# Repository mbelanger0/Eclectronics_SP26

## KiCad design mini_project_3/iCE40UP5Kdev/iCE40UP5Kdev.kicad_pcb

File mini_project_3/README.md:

# Mini Project 3 - iCE40UP5 Development Board

# Project Overview
The goal fo this project was to create a development board layout for the Lattice iCE40UP5 FPGA that is as close in size as possible to a Raspberry Pi Pico.

My implementation is located in the `iCE40UP5Kdev` directory.

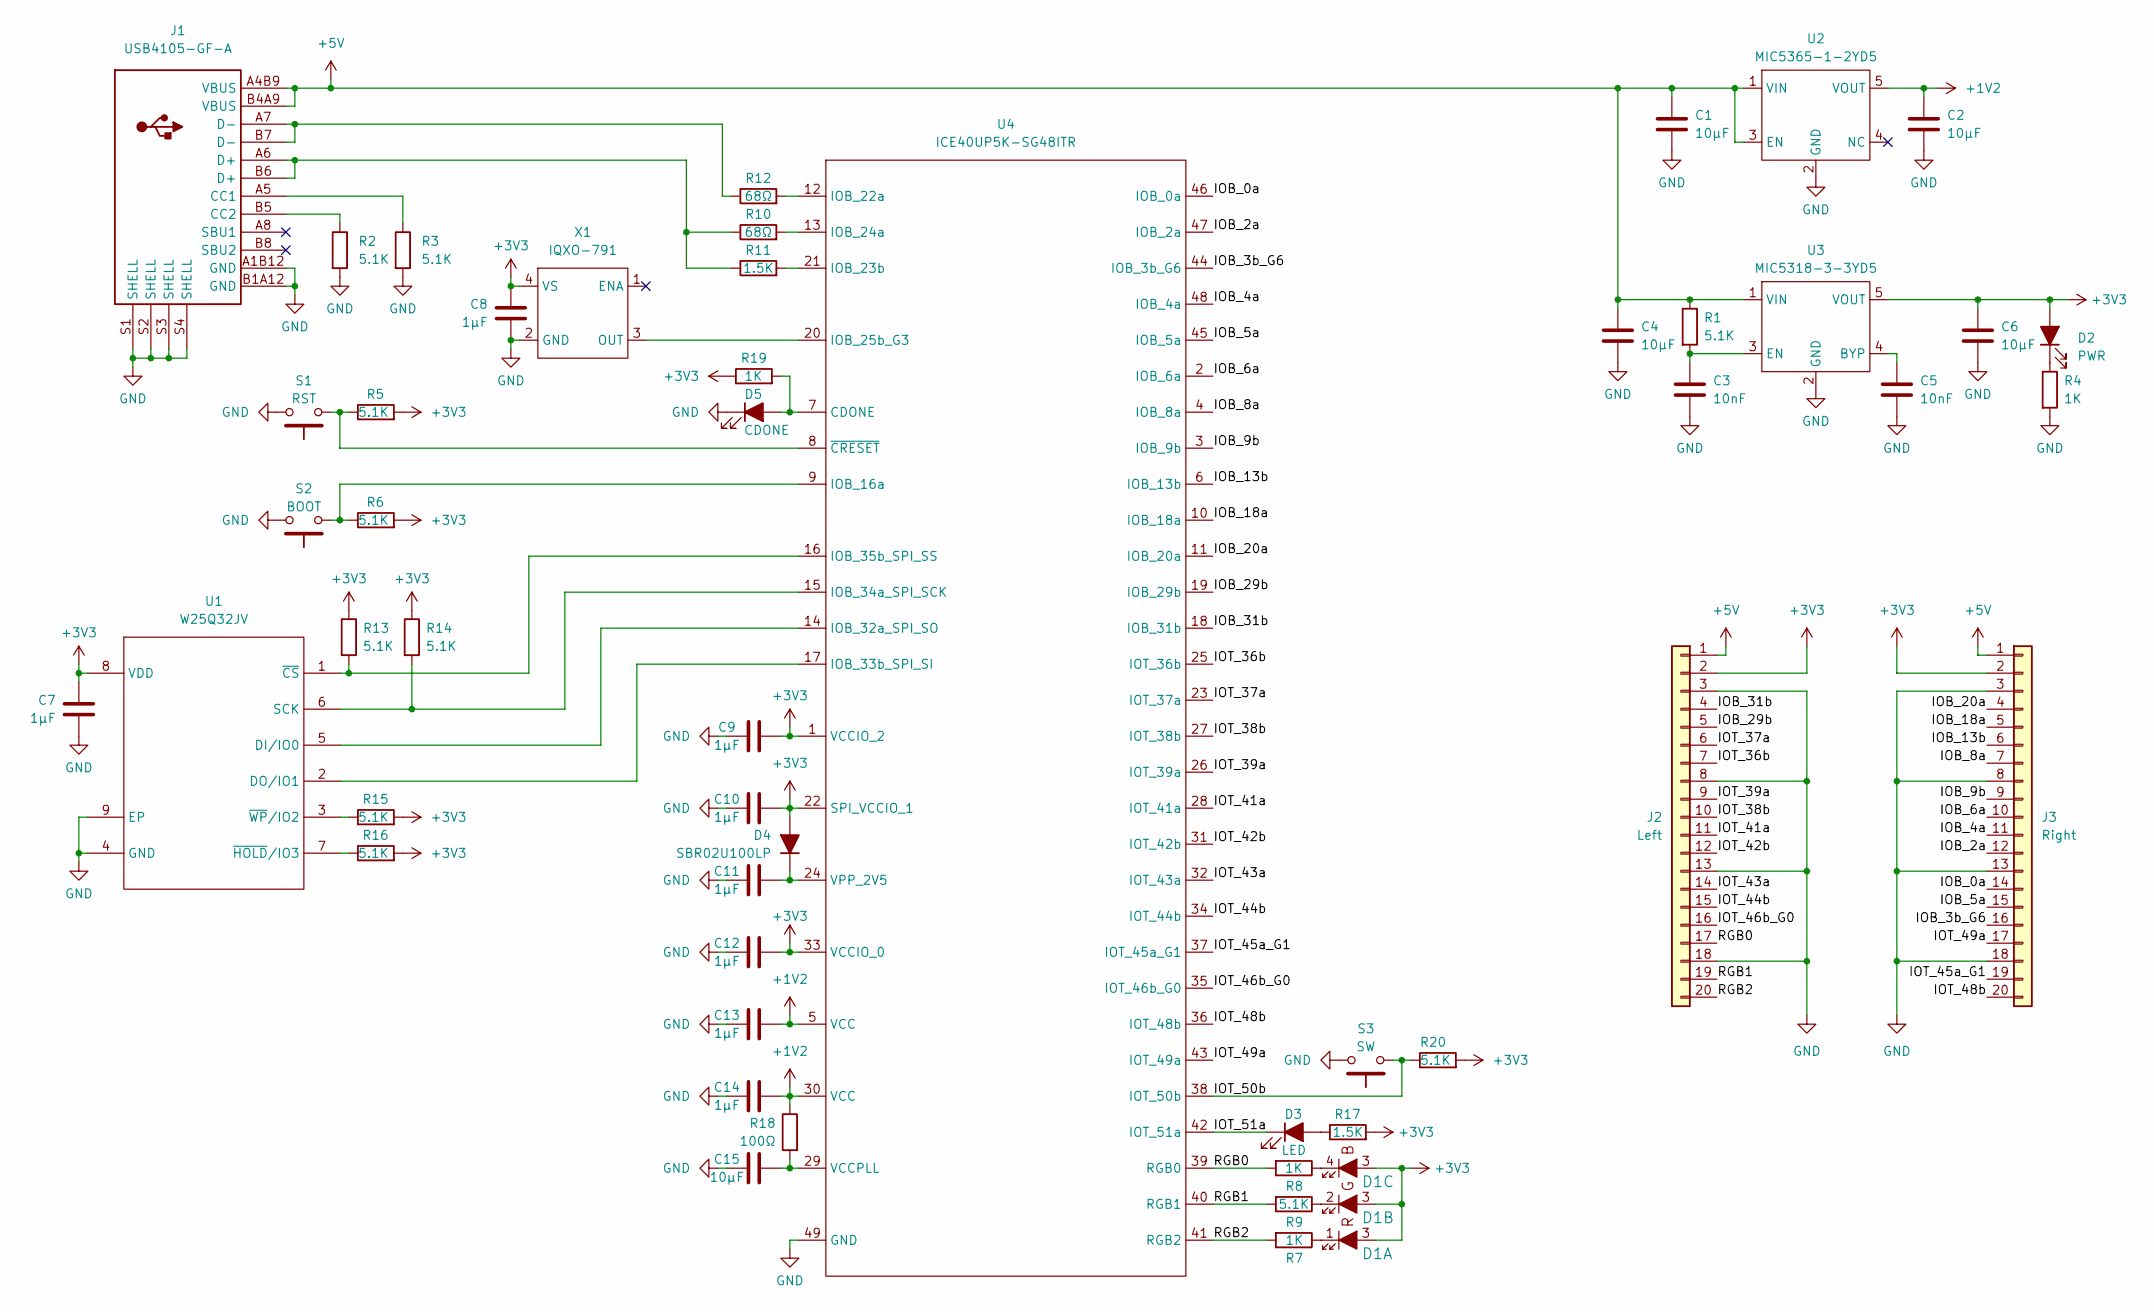
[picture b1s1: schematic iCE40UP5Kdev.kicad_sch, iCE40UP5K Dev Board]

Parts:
C1, C2, C4, C6, C15: 10µF; C_0603_1608Metric
C3, C5: 10nF; C_0603_1608Metric
C7, C8, C9, C10, C11, C12, C13, C14: 1µF; C_0402_1005Metric
D1: IN-S85TATRGB_ALT; IN-S85TATRGB
D2: PWR; LED_0805_2012Metric
D3: LED; LED_0805_2012Metric
D4: SBR02U100LP; D_0402_1005Metric
D5: CDONE; LED_0805_2012Metric
J1: USB4105-GF-A
J2: Left; PinHeader_1x20_P2.54mm_Vertical
J3: Right; PinHeader_1x20_P2.54mm_Vertical
R1, R2, R3, R5, R6, R9, R20: 5.1K; R_0603_1608Metric
R4, R7, R8, R19: 1K; R_0603_1608Metric
R10, R12: 68Ω; R_0402_1005Metric
R11: 1.5K; R_0402_1005Metric
R13, R14, R15, R16: 5.1K; R_0402_1005Metric
R17: 1.5K; R_0603_1608Metric
R18: 100Ω; R_0402_1005Metric
S1: RST; SW_SPST_B3U-1000P
S2: BOOT; SW_SPST_B3U-1000P
S3: SW; SW_SPST_B3U-1000P
U1: W25Q32JV; WSON-8-1EP_6x5mm_P1.27mm_EP3.4x4.3mm
U2: MIC5365-1-2YD5; TSOT-23-5
U3: MIC5318-3-3YD5; TSOT-23-5
U4: ICE40UP5K-SG48ITR; QFN-48-1EP_7x7mm_P0.5mm_EP5.6x5.6mm
X1: IQXO-791

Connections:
+1V2: C2.1, C13.2, C14.2, R18.1, U2.5 (VOUT), U4.5 (VCC), U4.30 (VCC)
+3V3: C6.1, C7.1, C8.1, C9.2, C10.2, C12.2, D1.3, D2.2 (A), D4.2 (A), J2.2, J3.2, R5.2, R6.2, R13.1, R14.1, R15.2, R16.2, R17.2, R19.1, R20.2, U1.8 (VDD), U3.5 (VOUT), U4.1 (VCCIO_2), U4.22 (SPI_VCCIO_1), U4.33 (VCCIO_0), X1.4 (VS)
+5V: C1.1, C4.1, J1.A4B9 (VBUS), J1.B4A9 (VBUS), J2.1, J3.1, R1.1, U2.1 (VIN), U2.3 (EN), U3.1 (VIN)
/IOB_0a: J3.14, U4.46 (IOB_0a)
/IOB_2a: J3.12, U4.47 (IOB_2a)
/IOB_3b_G6: J3.16, U4.44 (IOB_3b_G6)
/IOB_4a: J3.11, U4.48 (IOB_4a)
/IOB_5a: J3.15, U4.45 (IOB_5a)
/IOB_6a: J3.10, U4.2 (IOB_6a)
/IOB_8a: J3.7, U4.4 (IOB_8a)
/IOB_9b: J3.9, U4.3 (IOB_9b)
/IOB_13b: J3.6, U4.6 (IOB_13b)
/IOB_18a: J3.5, U4.10 (IOB_18a)
/IOB_20a: J3.4, U4.11 (IOB_20a)
/IOB_29b: J2.5, U4.19 (IOB_29b)
/IOB_31b: J2.4, U4.18 (IOB_31b)
/IOT_36b: J2.7, U4.25 (IOT_36b)
/IOT_37a: J2.6, U4.23 (IOT_37a)
/IOT_38b: J2.10, U4.27 (IOT_38b)
/IOT_39a: J2.9, U4.26 (IOT_39a)
/IOT_41a: J2.11, U4.28 (IOT_41a)
/IOT_42b: J2.12, U4.31 (IOT_42b)
/IOT_43a: J2.14, U4.32 (IOT_43a)
/IOT_44b: J2.15, U4.34 (IOT_44b)
/IOT_45a_G1: J3.19, U4.37 (IOT_45a_G1)
/IOT_46b_G0: J2.16, U4.35 (IOT_46b_G0)
/IOT_48b: J3.20, U4.36 (IOT_48b)
/IOT_49a: J3.17, U4.43 (IOT_49a)
/IOT_50b: R20.1, S3.1, U4.38 (IOT_50b)
/IOT_51a: D3.1 (K), U4.42 (IOT_51a)
/RGB0: J2.17, R8.2, U4.39 (RGB0)
/RGB1: J2.19, R9.2, U4.40 (RGB1)
/RGB2: J2.20, R7.2, U4.41 (RGB2)
GND: C1.2, C2.2, C3.2, C4.2, C5.2, C6.2, C7.2, C8.2, C9.1, C10.1, C11.1, C12.1, C13.1, C14.1, C15.1, D5.1 (K), J1.A1B12 (GND), J1.B1A12 (GND), J1.S1 (SHELL), J1.S2 (SHELL), J1.S3 (SHELL), J1.S4 (SHELL), J2.3, J2.8, J2.13, J2.18, J3.3, J3.8, J3.13, J3.18, R2.2, R3.2, R4.2, S1.2, S2.2, S3.2, U1.4 (GND), U1.9 (EP), U2.2 (GND), U3.2 (GND), U4.49 (GND), X1.2 (GND)
unnamed: D1.1, R7.1
unnamed: D1.2, R9.1
unnamed: D1.4, R8.1
unnamed: D2.1 (K), R4.1
unnamed: D3.2 (A), R17.1
unnamed: C11.2, D4.1 (K), U4.24 (VPP_2V5)
unnamed: D5.2 (A), R19.2, U4.7 (CDONE)
unnamed: J1.A5 (CC1), R3.1
unnamed: J1.B5 (CC2), R2.1
unnamed: J1.A6 (D+), J1.B6 (D+), R10.1, R11.1
unnamed: J1.A7 (D-), J1.B7 (D-), R12.1
unnamed: U1.5 (DI/IO0), U4.14 (IOB_32a_SPI_SO)
unnamed: U1.2 (DO/IO1), U4.17 (IOB_33b_SPI_SI)
unnamed: R14.2, U1.6 (SCK), U4.15 (IOB_34a_SPI_SCK)
unnamed: R13.2, U1.1 (~CS), U4.16 (IOB_35b_SPI_SS)
unnamed: R16.1, U1.7 (~HOLD/IO3)
unnamed: R15.1, U1.3 (~WP/IO2)
unnamed: C5.1, U3.4 (BYP)
unnamed: C3.1, R1.2, U3.3 (EN)
unnamed: R6.1, S2.1, U4.9 (IOB_16a)
unnamed: R12.2, U4.12 (IOB_22a)
unnamed: R11.2, U4.21 (IOB_23b)
unnamed: R10.2, U4.13 (IOB_24a)
unnamed: U4.20 (IOB_25b_G3), X1.3 (OUT)
unnamed: C15.2, R18.2, U4.29 (VCCPLL)
unnamed: R5.1, S1.1, U4.8 (~CRESET)

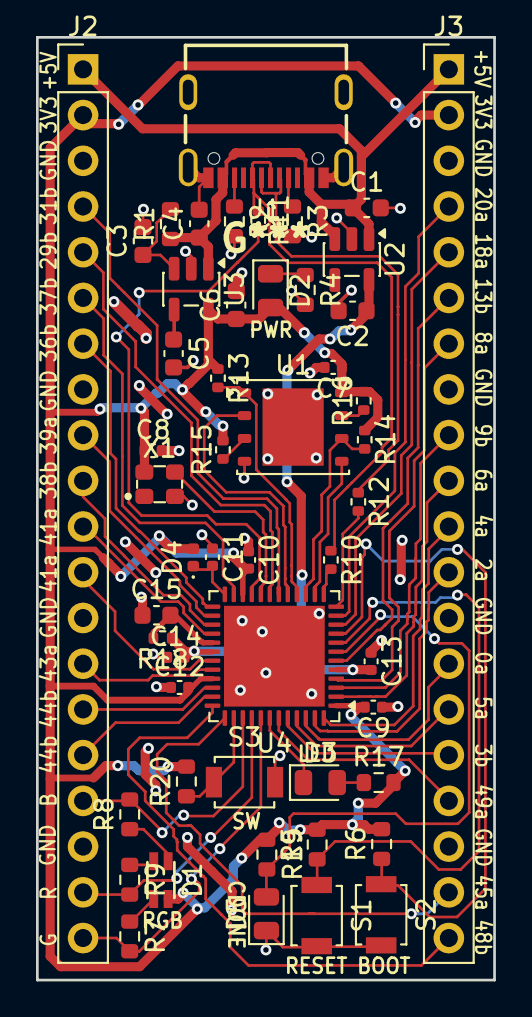
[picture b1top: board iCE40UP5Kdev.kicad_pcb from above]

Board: 2 copper layers, 25.4 x 52.4 mm, 51 parts (0 on the bottom side), 60 nets.

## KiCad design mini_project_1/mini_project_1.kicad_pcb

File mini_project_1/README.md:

# Mini Project 1: Hysteretic Oscillator

The goal of this project is to design a circuit and PCB to blink an LED at 1Hz +/- 10% using a hysteretic oscillator implemented with an op-amp. The project includes simulation and worst-case analysis to verify the behavior of the circuit.

## File Structure
- KiCad files are in this directory along with symbol/model imports
- Simulations are located in `simulation`. Nominal simulation is titled `mini_project_1.asc` while worst-case sim is titled `mini_project_1_worst_case.asc`
- The report is located in the `report` directory and is titled `report.pdf`

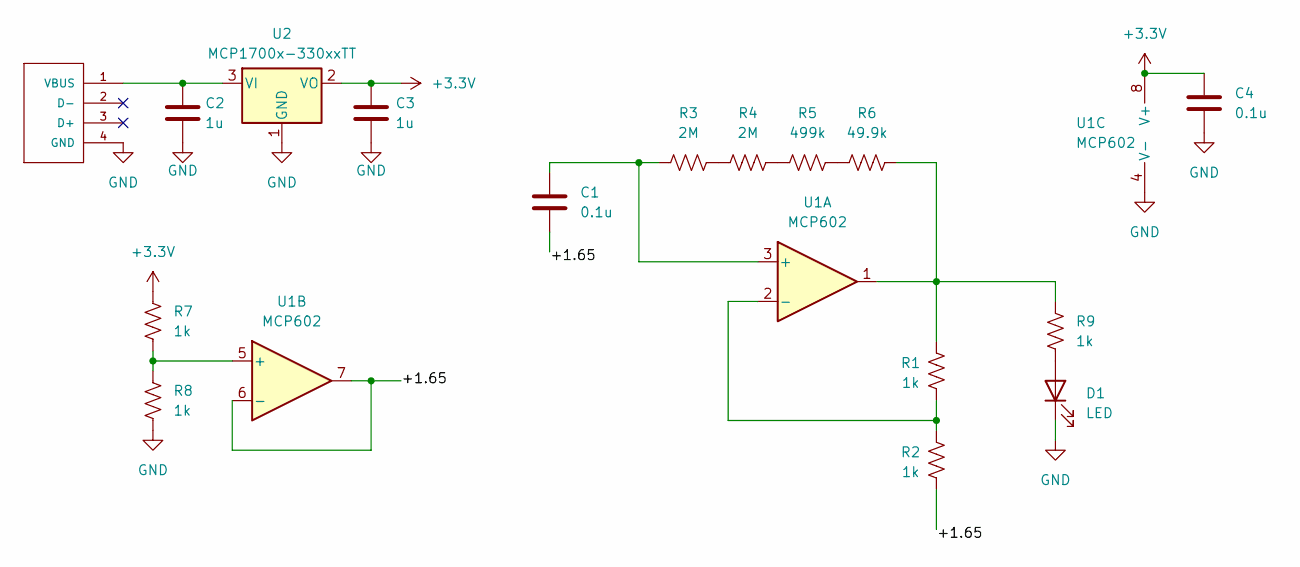
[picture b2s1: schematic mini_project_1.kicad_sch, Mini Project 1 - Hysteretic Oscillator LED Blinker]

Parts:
C1, C4: 0.1u; C_0603_1608Metric
C2, C3: 1u; C_0603_1608Metric
D1: LED; LED_0805_2012Metric
J1: 480370001; CONN_480370001_MOL; MANUFACTURER_PART_NUMBER 480370001
R1, R2, R7, R8, R9: 1k; R_0603_1608Metric
R3, R4: 2M; R_0603_1608Metric
R5: 499k; R_0603_1608Metric
R6: 49.9k; R_0603_1608Metric
U1: MCP602; TSSOP-8_4.4x3mm_P0.65mm
U2: MCP1700x-330xxTT; SOT-23

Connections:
+3.3V: C3.1, C4.1, R7.1, U1.8 (V+), U2.2 (VO); also elsewhere on the board
/+1.65: C1.2, R2.1, U1.6 (-), U1.7; also elsewhere on the board
GND: C2.2, C3.2, C4.2, D1.1 (K), J1.4 (GND), R8.2, U1.4 (V-), U2.1 (GND); also elsewhere on the board
unnamed: D1.2 (A), R9.2
unnamed: C2.1, J1.1 (VBUS), U2.3 (VI)
unnamed 5: R1.2, R6.2, R9.1, U1.1; also elsewhere on the board
unnamed: R3.2, R4.1
unnamed: R4.2, R5.1
unnamed: R5.2, R6.1
unnamed 9: C1.1, R3.1, U1.3 (+); also elsewhere on the board
unnamed 10: R1.1, R2.2, U1.2 (-); also elsewhere on the board
unnamed 11: R7.2, R8.1, U1.5 (+); also elsewhere on the board

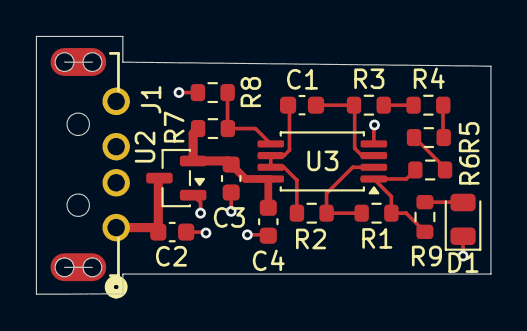
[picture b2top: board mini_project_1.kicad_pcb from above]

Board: 2 copper layers, 25.2 x 14.3 mm, 17 parts (0 on the bottom side), 12 nets.

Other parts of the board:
U3: MCP602; TSSOP-8_4.4x3mm_P0.65mm

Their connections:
+3.3V: U3.8 (V+); also elsewhere on the board
/+1.65: U3.6 (-), U3.7; also elsewhere on the board
GND: U3.4 (V-); also elsewhere on the board
unnamed 5: U3.1; also elsewhere on the board
unnamed 9: U3.3 (+); also elsewhere on the board
unnamed 10: U3.2 (-); also elsewhere on the board
unnamed 11: U3.5 (+); also elsewhere on the board

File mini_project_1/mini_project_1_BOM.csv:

"Reference","Qty","Value","DNP","Exclude from BOM","Exclude from Board","Footprint","Datasheet"
"C1,C4","2","0.1u","","","","Capacitor_SMD:C_0603_1608Metric","~"
"C2,C3","2","1u","","","","Capacitor_SMD:C_0603_1608Metric","~"
"D1","1","LED","","","","LED_SMD:LED_0805_2012Metric","~"
"J1","1","480370001","","","","480370001:CONN_480370001_MOL",""
"R1,R2,R7,R8,R9","5","1k","","","","Resistor_SMD:R_0603_1608Metric","~"
"R3,R4","2","2M","","","","Resistor_SMD:R_0603_1608Metric","~"
"R5","1","499k","","","","Resistor_SMD:R_0603_1608Metric","~"
"R6","1","49.9k","","","","Resistor_SMD:R_0603_1608Metric","~"
"U1","1","MCP602","","","","Package_SO:TSSOP-8_4.4x3mm_P0.65mm","http://ww1.microchip.com/downloads/en/DeviceDoc/21314g.pdf"
"U2","1","MCP1700x-330xxTT","","","","Package_TO_SOT_SMD:SOT-23","http://ww1.microchip.com/downloads/en/DeviceDoc/20001826D.pdf"

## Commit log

2026-01-28 Add schematic and SPICE sim for mini project 1
2026-01-28 Add initial README
2026-01-29 Create preliminary layout
2026-01-29 Use op amp buffer for 1.65V net
2026-01-30 Add sim for buffer supplied 1.65v
2026-02-02 Modify schematic, layout, and add report
2026-02-08 Add complete schematic, layout, report, sim
2026-02-08 Final layout changes
2026-02-08 Add pdf of schematic
2026-02-09 Add project repo link to report
2026-02-18 Add mini project 2 video
2026-02-24 Add mini project 3 starter files
2026-02-24 Set footprints for mini project 3
2026-02-24 Add start to layout of mini project 3
2026-02-26 Add more components to layout
2026-02-26 Add more layout progress
2026-02-26 Add layout with all components and most traces
2026-02-27 Add nearly complete layout
    Planning on trying to reduce the size of the board
    by 100 mills after this commit to match the size
    of a RasPi Pico
2026-03-02 Add silkscreen to mini project 3
2026-03-05 Add more silkscreen for MP3
2026-03-05 Fix via size, silkscreen, and add README
2026-03-05 Update README with implementation directory details
    Added implementation directory information to README.
2026-03-06 Add minor layout changes to MP3
2026-03-30 Add videos of working board
